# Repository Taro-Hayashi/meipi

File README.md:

# meipi

BOOTHで商品を購入すると付いてくることがあります。名刺代わりにお配りしているもので、組み立てるにもパーツを揃える必要がありますのでご随意にしていただければ幸いです。

## パーツリスト

### 共通パーツ
|Ref|部品名|
|-|-|
||キースイッチ|
||キーキャップ|
||CherryMXホットスワップソケット|
||1N4148W|
||MJ-4PP-9, PJ-320A|
|BOOT, RUN|3x6x4.3タクタイルスイッチ|
||Pro Micro|

### ロータリーエンコーダー
|Ref|部品名|
|-|-|
||EC11, EC12|
||ノブ|

### LED
|Ref|部品名|
|-|-|
|U1|NCP1117, ADP3338|
|LED0-12|SK6812MINI-E|

### OLED
|Ref|部品名|
|-|-|
||OLEDモジュール|
||ピンソケット 4ピン分|
||ピンヘッダ 4ピン分|

### トラックボール
|Ref|部品名|
|-|-|
||PIM447|
||3.5mmピンソケット 5ピン分|
||7mmスペーサー|
||ネジ|

### ジョイスティック
|Ref|部品名|
|-|-|
||RKJXV1224005 DIP化キット|
||キャップ|
|JOYSTICK0|L型ピンソケット 1x6（6p)|
|JOYSTICK1|ピンソケット 6ピン分|

### RP2040

頒布している基板には2種類あり、写真の位置に穴が空いている場合はRP2040の手はんだが可能です。
とても難しいので他のパーツより先にはんだ付けをしてください。
#### 表面実装部品
|Ref|部品名|
|-|-|
|RP2040|RP2040|
|U1|NCP1117, ADP3338|
|U2|W25Q（32MB〜）|
|USB0|USB Type-Cコネクタ 基板用|

#### 3225サイズ
|Ref|部品名|
|-|-|
|Y1|12MHz 水晶振動子|

#### 1206サイズ
|Ref|部品名|
|-|-|
|R1,2|5.1k|
|R3,4|27|
|R5|10k|
|R6-8|1k|
|C1,2|10u|
|C3|1u|
|C4,5|0.1u|
|C6|1u|
|C7-14|0.1u|
|C15,16|27p|

## ファームウェア
https://github.com/Taro-Hayashi/qmk_firmware/tree/tarohayashi/keyboards/tarohayashi/archive/meipi

### そのほか

atushi Morimoto様のフットプリントを改変、流用させていただきました。  
https://github.com/74th/rp2040-dev-board

takashicompany様のフットプリントを改変、流用させていただきました。  
https://github.com/takashicompany/tkbd-lib  
  
<br /><a rel="license" href="http://creativecommons.org/licenses/by-sa/4.0/">クリエイティブ・コモンズ 表示 - 継承 4.0 国際 ライセンス</a>の下に提供されています。

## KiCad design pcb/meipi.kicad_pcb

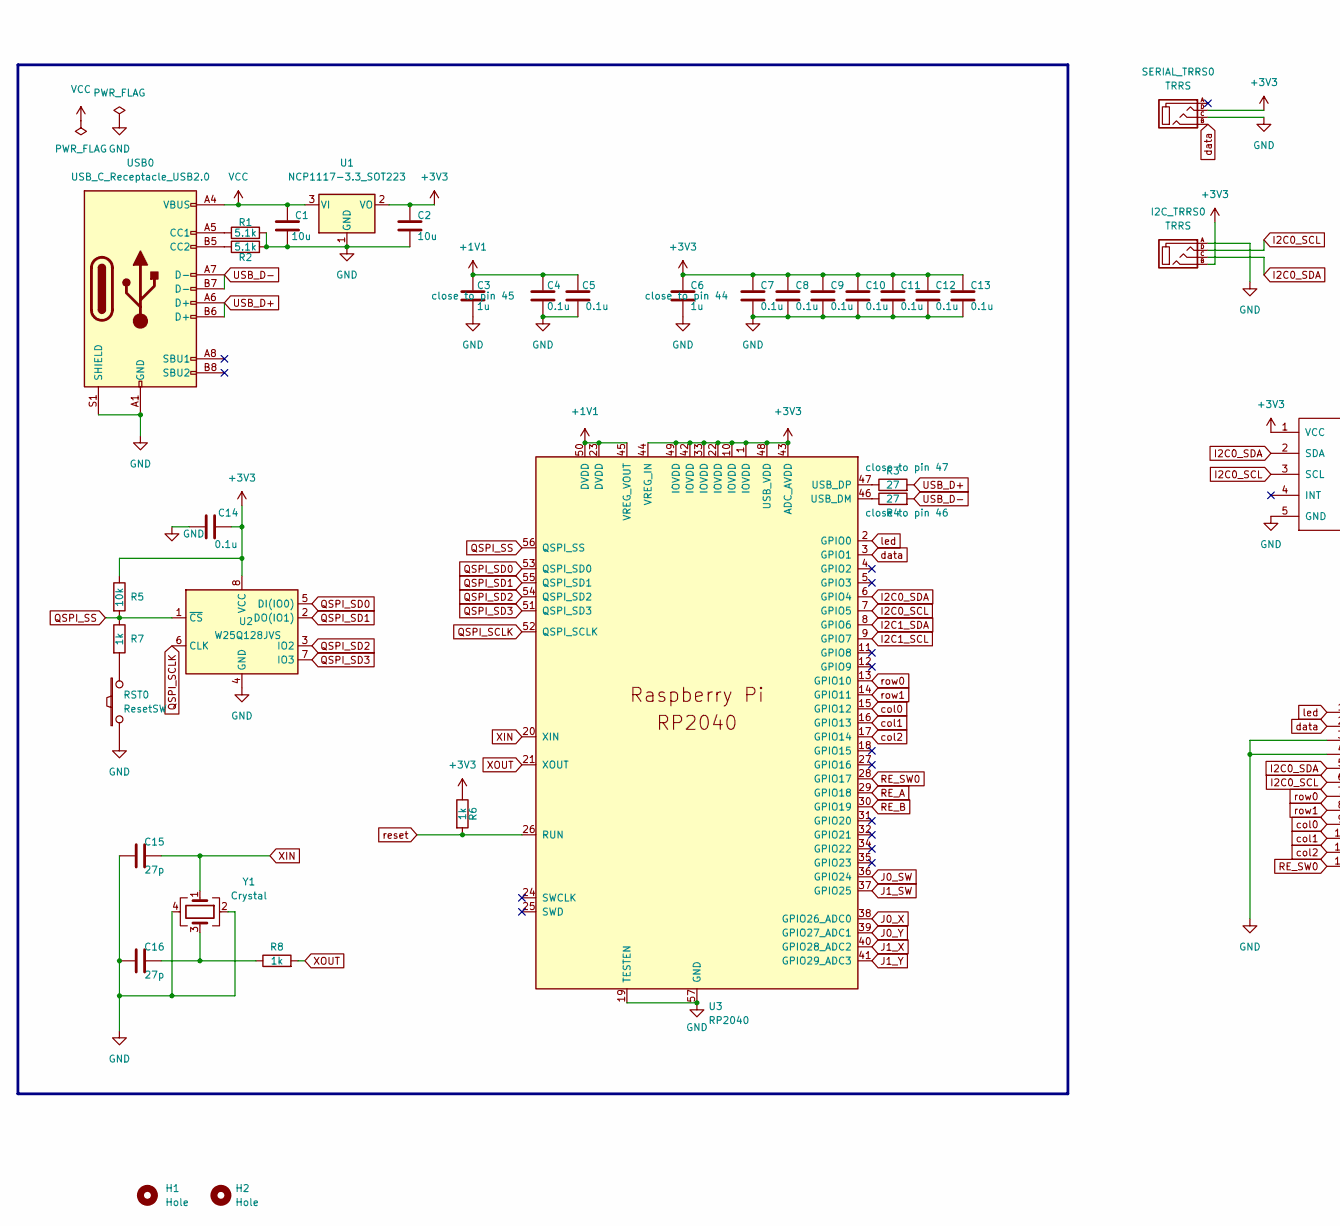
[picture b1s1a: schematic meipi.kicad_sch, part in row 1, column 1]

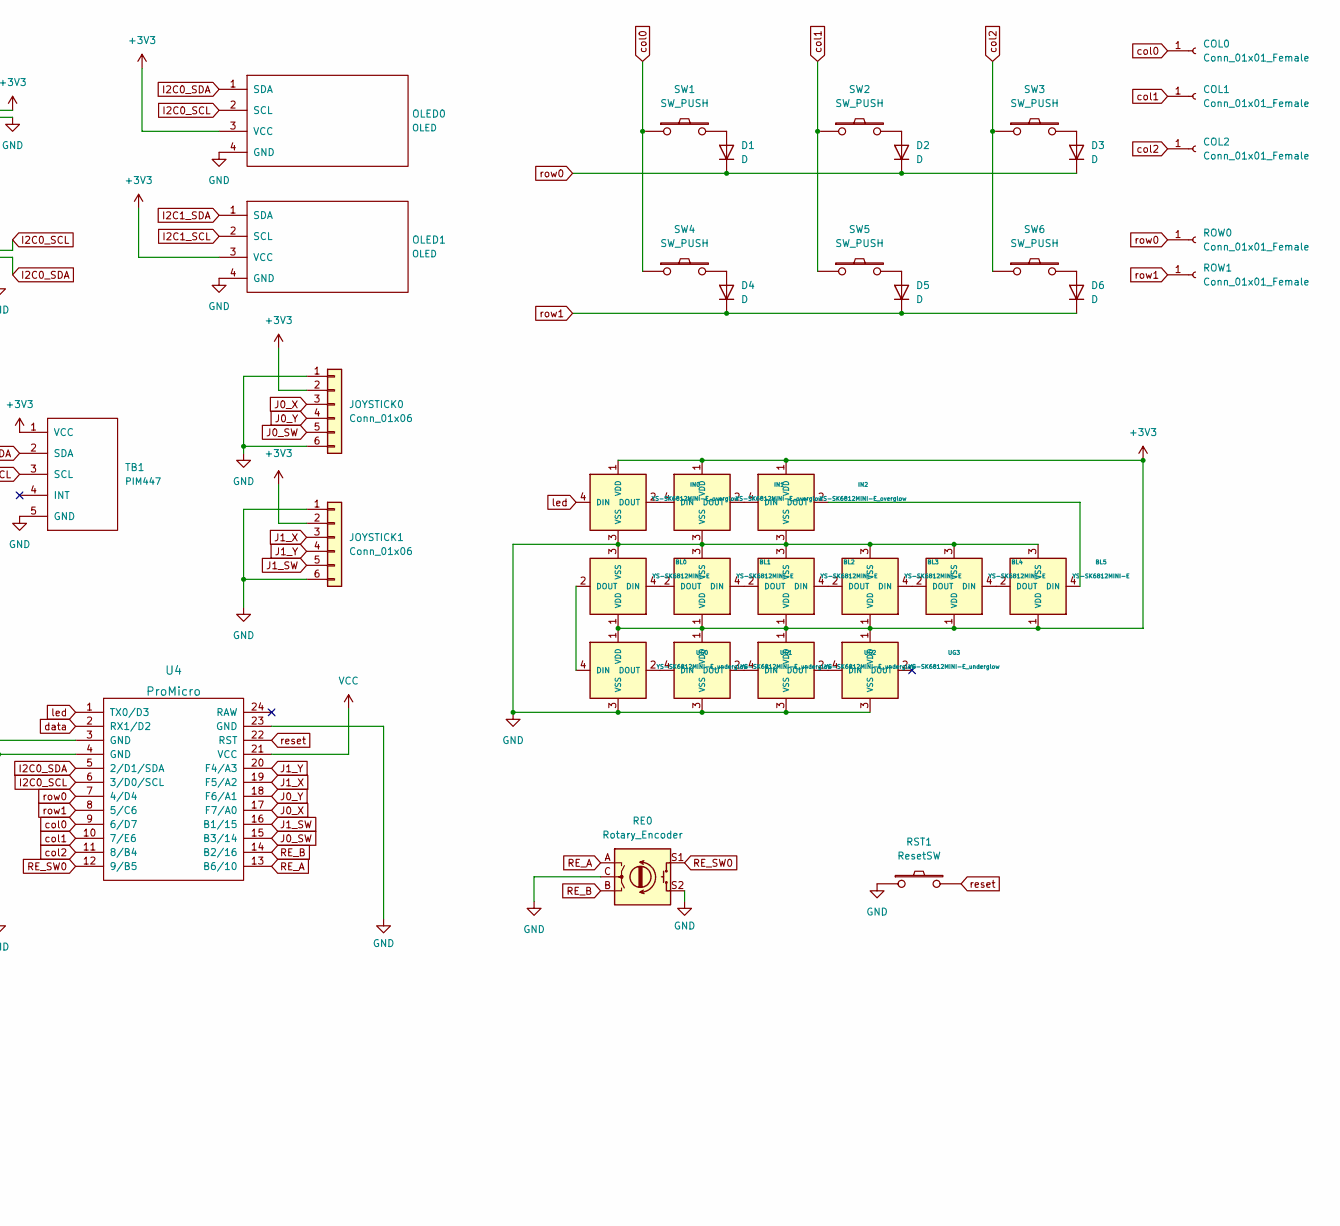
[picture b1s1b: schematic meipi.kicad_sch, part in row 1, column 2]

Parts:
BL0, BL1, BL2, BL3, BL4, BL5: YS-SK6812MINI-E
C1, C2: 10u; C_1206_3216_SMD
C3, C6: 1u; C_1206_3216_SMD
C4, C5, C7, C8, C9, C10, C11, C12, C13, C14: 0.1u; C_1206_3216_SMD
C15, C16: 27p; C_1206_3216_SMD
COL0, COL1, COL2: Conn_01x01_Female; Conn_1.3mm_M2
D1, D2, D3, D4, D5, D6: D; Diode_SMD
H1, H2: Hole; Hole_2.2mm_M2
I2C_TRRS0: TRRS
IN0, IN1, IN2: YS-SK6812MINI-E_overglow; YS-SK6812MINI-E
JOYSTICK0: Conn_01x06; PinSocket_1x06_P2.54mm_Horizontal
JOYSTICK1: Conn_01x06; PinHeader_1x06_P2.54mm_Vertical
OLED0, OLED1: OLED
R1, R2: 5.1k; R_1206_3216_SMD
R3, R4: 27; R_1206_3216_SMD
R5: 10k; R_1206_3216_SMD
R6, R7, R8: 1k; R_1206_3216_SMD
RE0: Rotary_Encoder; RotaryEncoder
ROW0, ROW1: Conn_01x01_Female; Conn_1.3mm_M2
RST0, RST1: ResetSW
SERIAL_TRRS0: TRRS
SW1, SW2, SW3, SW4, SW5, SW6: SW_PUSH; MXOnly-1U-Hotswap
TB1: PIM447
U1: NCP1117-3.3_SOT223; SOT-223-3_TabPin2
U2: W25Q128JVS; SOIC-8_5.23x5.23mm_P1.27mm
U3: RP2040; RP2040-QFN-56
U4: ProMicro; ProMicro_back_usd
UG0, UG1, UG2, UG3: YS-SK6812MINI-E_underglow; YS-SK6812MINI-E_Undergrow
USB0: USB_C_Receptacle_USB2.0
Y1: Crystal; Crystal_3225_SMD

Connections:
+1V1: C3.1, C4.1, C5.1, U3.23 (DVDD), U3.45 (VREG_VOUT), U3.50 (DVDD); also elsewhere on the board
+3V3: BL0.1 (VDD), BL1.1 (VDD), BL2.1 (VDD), BL3.1 (VDD), BL4.1 (VDD), BL5.1 (VDD), C2.1, C6.1, C7.1, C8.1, C9.1, C10.1, C11.1, C12.1, C13.1, C14.1, I2C_TRRS0.B, IN0.1 (VDD), IN1.1 (VDD), IN2.1 (VDD), JOYSTICK0.2, JOYSTICK1.2, OLED0.3 (VCC), OLED1.3 (VCC), R5.1, R6.1, SERIAL_TRRS0.D, TB1.1 (VCC), U1.2 (VO), U2.8 (VCC), U3.1 (IOVDD), U3.10 (IOVDD), U3.22 (IOVDD), U3.33 (IOVDD), U3.42 (IOVDD), U3.43 (ADC_AVDD), U3.44 (VREG_IN), U3.48 (USB_VDD), U3.49 (IOVDD), UG0.1 (VDD), UG1.1 (VDD), UG2.1 (VDD), UG3.1 (VDD); also elsewhere on the board
GND: BL0.3 (VSS), BL1.3 (VSS), BL2.3 (VSS), BL3.3 (VSS), BL4.3 (VSS), BL5.3 (VSS), C1.1, C2.2, C3.2, C4.2, C5.2, C6.2, C7.2, C8.2, C9.2, C10.2, C11.2, C12.2, C13.2, C14.2, C15.1, C16.1, I2C_TRRS0.A, IN0.3 (VSS), IN1.3 (VSS), IN2.3 (VSS), JOYSTICK0.1, JOYSTICK0.6, JOYSTICK1.1, JOYSTICK1.6, OLED0.4 (GND), OLED1.4 (GND), R1.2, R2.2, RE0.C, RE0.S2, RST0.1, RST1.1, SERIAL_TRRS0.C, TB1.5 (GND), U1.1 (GND), U2.4 (GND), U3.19 (TESTEN), U3.57 (GND), U4.3 (GND), U4.4 (GND), U4.23 (GND), UG0.3 (VSS), UG1.3 (VSS), UG2.3 (VSS), UG3.3 (VSS), USB0.A1 (GND), USB0.A12 (GND), USB0.B1 (GND), USB0.B12 (GND), USB0.S1 (SHIELD), Y1.2, Y1.4; also elsewhere on the board
I2C0_SCL: I2C_TRRS0.D, OLED0.2 (SCL), TB1.3 (SCL), U3.7 (GPIO5), U4.6 (3/D0/SCL); also elsewhere on the board
I2C0_SDA: I2C_TRRS0.C, OLED0.1 (SDA), TB1.2 (SDA), U3.6 (GPIO4), U4.5 (2/D1/SDA); also elsewhere on the board
I2C1_SCL: OLED1.2 (SCL), U3.9 (GPIO7); also elsewhere on the board
I2C1_SDA: OLED1.1 (SDA), U3.8 (GPIO6); also elsewhere on the board
J0_SW: JOYSTICK0.5, U3.36 (GPIO24), U4.15 (B3/14); also elsewhere on the board
J0_X: JOYSTICK0.3, U3.38 (GPIO26_ADC0), U4.17 (F7/A0); also elsewhere on the board
J0_Y: JOYSTICK0.4, U3.39 (GPIO27_ADC1), U4.18 (F6/A1); also elsewhere on the board
J1_SW: JOYSTICK1.5, U3.37 (GPIO25), U4.16 (B1/15); also elsewhere on the board
J1_X: JOYSTICK1.3, U3.40 (GPIO28_ADC2), U4.19 (F5/A2); also elsewhere on the board
J1_Y: JOYSTICK1.4, U3.41 (GPIO29_ADC3), U4.20 (F4/A3); also elsewhere on the board
unnamed: BL0.2 (DOUT), UG0.4 (DIN)
unnamed: BL0.4 (DIN), BL1.2 (DOUT)
unnamed: BL1.4 (DIN), BL2.2 (DOUT)
unnamed: BL2.4 (DIN), BL3.2 (DOUT)
unnamed: BL3.4 (DIN), BL4.2 (DOUT)
unnamed: BL4.4 (DIN), BL5.2 (DOUT)
unnamed: BL5.4 (DIN), IN2.2 (DOUT)
unnamed: C16.2, R8.1, Y1.3
unnamed: D1.2 (A), SW1.2
unnamed: D2.2 (A), SW2.2
unnamed: D3.2 (A), SW3.2
unnamed: D4.2 (A), SW4.2
unnamed: D5.2 (A), SW5.2
unnamed: D6.2 (A), SW6.2
unnamed: IN0.2 (DOUT), IN1.4 (DIN)
unnamed: IN1.2 (DOUT), IN2.4 (DIN)
unnamed 29: R3.1, U3.47 (USB_DP); also elsewhere on the board
unnamed 30: R4.1, U3.46 (USB_DM); also elsewhere on the board
unnamed: R7.2, RST0.2
unnamed: UG0.2 (DOUT), UG1.4 (DIN)
unnamed: UG1.2 (DOUT), UG2.4 (DIN)
unnamed: UG2.2 (DOUT), UG3.4 (DIN)
unnamed: R1.1, USB0.A5 (CC1)
unnamed: R2.1, USB0.B5 (CC2)
QSPI_SCLK: U2.6 (CLK), U3.52 (QSPI_SCLK); also elsewhere on the board
QSPI_SD0: U2.5 (DI(IO0)), U3.53 (QSPI_SD0); also elsewhere on the board
QSPI_SD1: U2.2 (DO(IO1)), U3.55 (QSPI_SD1); also elsewhere on the board
QSPI_SD2: U2.3 (IO2), U3.54 (QSPI_SD2); also elsewhere on the board
QSPI_SD3: U2.7 (IO3), U3.51 (QSPI_SD3); also elsewhere on the board
QSPI_SS: R5.2, R7.1, U2.1 (~CS), U3.56 (QSPI_SS); also elsewhere on the board
RE_A: RE0.A, U3.29 (GPIO18), U4.13 (B6/10); also elsewhere on the board
RE_B: RE0.B, U3.30 (GPIO19), U4.14 (B2/16); also elsewhere on the board
RE_SW0: RE0.S1, U3.28 (GPIO17), U4.12 (9/B5); also elsewhere on the board
USB_D+: R3.2, USB0.A6 (D+), USB0.B6 (D+)
USB_D-: R4.2, USB0.A7 (D-), USB0.B7 (D-)
VCC: C1.2, U1.3 (VI), U4.21 (VCC), USB0.A4 (VBUS), USB0.A9 (VBUS), USB0.B4 (VBUS), USB0.B9 (VBUS)
XIN: C15.2, U3.20 (XIN), Y1.1; also elsewhere on the board
XOUT: R8.2, U3.21 (XOUT); also elsewhere on the board
col0: COL0.1, SW1.1, SW4.1, U3.15 (GPIO12), U4.9 (6/D7); also elsewhere on the board
col1: COL1.1, SW2.1, SW5.1, U3.16 (GPIO13), U4.10 (7/E6); also elsewhere on the board
col2: COL2.1, SW3.1, SW6.1, U3.17 (GPIO14), U4.11 (8/B4); also elsewhere on the board
data: SERIAL_TRRS0.B, U3.3 (GPIO1), U4.2 (RX1/D2); also elsewhere on the board
led: IN0.4 (DIN), U3.2 (GPIO0), U4.1 (TX0/D3); also elsewhere on the board
reset: R6.2, RST1.2, U3.26 (RUN), U4.22 (RST); also elsewhere on the board
row0: D1.1 (K), D2.1 (K), D3.1 (K), ROW0.1, U3.13 (GPIO10), U4.7 (4/D4); also elsewhere on the board
row1: D4.1 (K), D5.1 (K), D6.1 (K), ROW1.1, U3.14 (GPIO11), U4.8 (5/C6); also elsewhere on the board

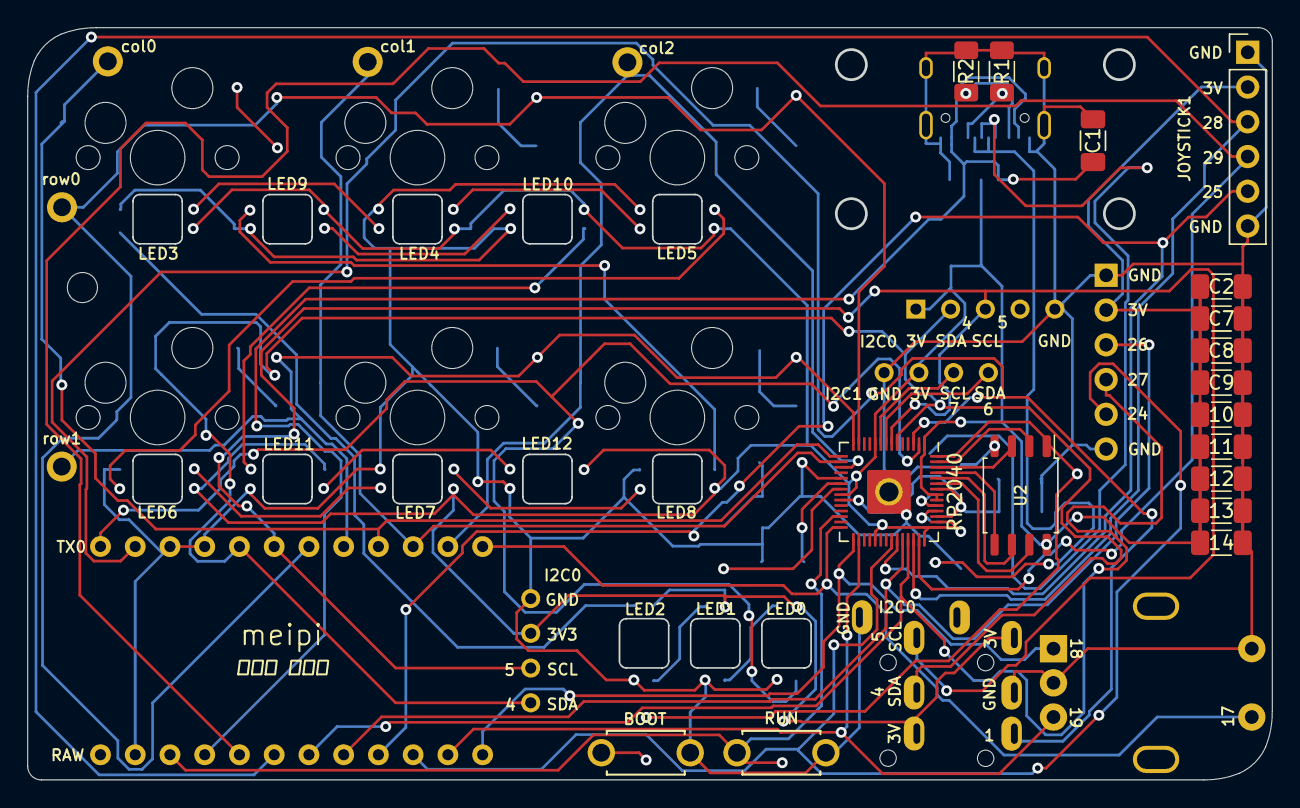
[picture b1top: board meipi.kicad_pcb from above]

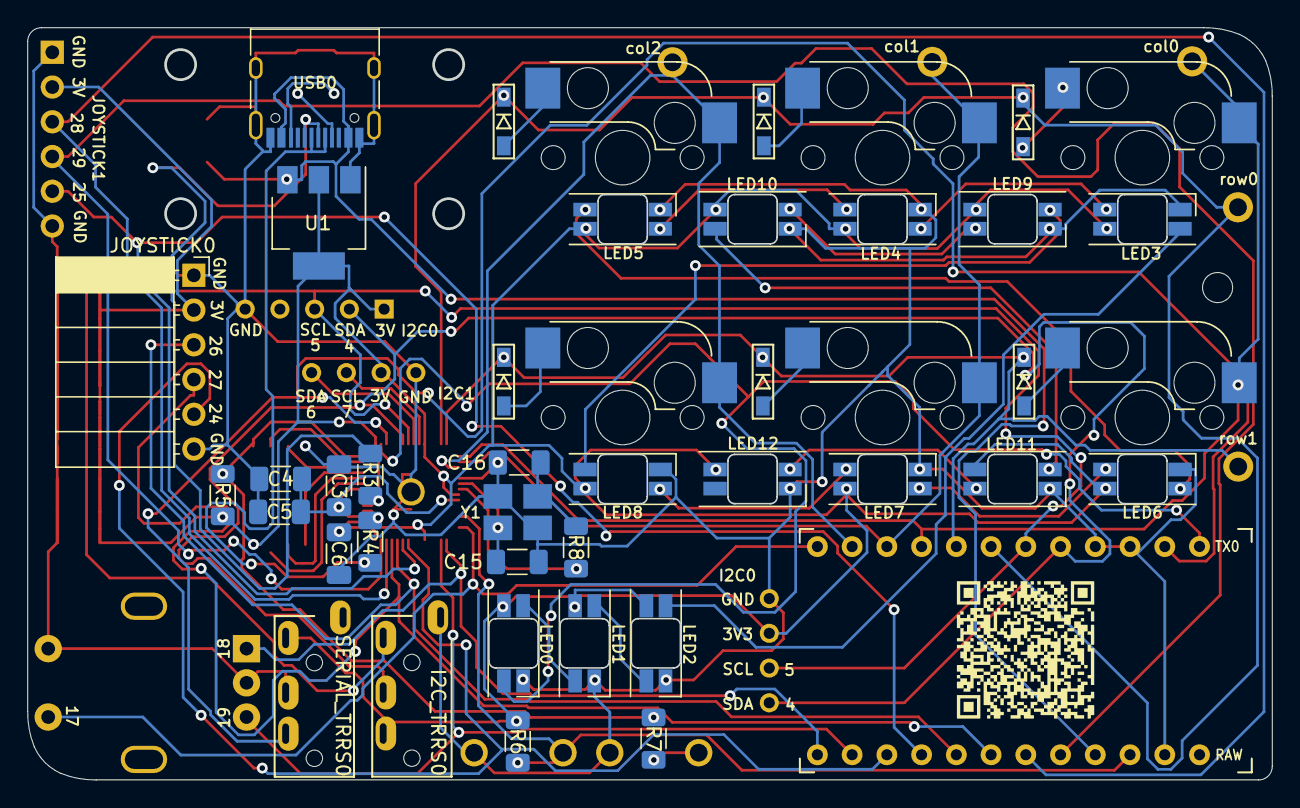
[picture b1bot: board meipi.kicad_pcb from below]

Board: 2 copper layers, 90.9 x 54.9 mm, 71 parts (33 on the bottom side), 59 nets.

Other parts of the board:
10, 11, 12, 13, 14: 0.1u; C_1206_3216_SMD
RP2040: RP2040; RP2040-QFN-56

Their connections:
+1V1: RP2040.23 (DVDD), RP2040.45 (VREG_VOUT), RP2040.50 (DVDD); also elsewhere on the board
+3V3: 10.1, 11.1, 12.1, 13.1, 14.1, RP2040.1 (IOVDD), RP2040.10 (IOVDD), RP2040.22 (IOVDD), RP2040.33 (IOVDD), RP2040.42 (IOVDD), RP2040.43 (ADC_AVDD), RP2040.44 (VREG_IN), RP2040.48 (USB_VDD), RP2040.49 (IOVDD); also elsewhere on the board
GND: 10.2, 11.2, 12.2, 13.2, 14.2, RP2040.19 (TESTEN), RP2040.57 (GND); also elsewhere on the board
I2C0_SCL: RP2040.7 (GPIO5); also elsewhere on the board
I2C0_SDA: RP2040.6 (GPIO4); also elsewhere on the board
I2C1_SCL: RP2040.9 (GPIO7); also elsewhere on the board
I2C1_SDA: RP2040.8 (GPIO6); also elsewhere on the board
J0_SW: RP2040.36 (GPIO24); also elsewhere on the board
J0_X: RP2040.38 (GPIO26_ADC0); also elsewhere on the board
J0_Y: RP2040.39 (GPIO27_ADC1); also elsewhere on the board
J1_SW: RP2040.37 (GPIO25); also elsewhere on the board
J1_X: RP2040.40 (GPIO28_ADC2); also elsewhere on the board
J1_Y: RP2040.41 (GPIO29_ADC3); also elsewhere on the board
unnamed 29: RP2040.47 (USB_DP); also elsewhere on the board
unnamed 30: RP2040.46 (USB_DM); also elsewhere on the board
QSPI_SCLK: RP2040.52 (QSPI_SCLK); also elsewhere on the board
QSPI_SD0: RP2040.53 (QSPI_SD0); also elsewhere on the board
QSPI_SD1: RP2040.55 (QSPI_SD1); also elsewhere on the board
QSPI_SD2: RP2040.54 (QSPI_SD2); also elsewhere on the board
QSPI_SD3: RP2040.51 (QSPI_SD3); also elsewhere on the board
QSPI_SS: RP2040.56 (QSPI_SS); also elsewhere on the board
RE_A: RP2040.29 (GPIO18); also elsewhere on the board
RE_B: RP2040.30 (GPIO19); also elsewhere on the board
RE_SW0: RP2040.28 (GPIO17); also elsewhere on the board
XIN: RP2040.20 (XIN); also elsewhere on the board
XOUT: RP2040.21 (XOUT); also elsewhere on the board
col0: RP2040.15 (GPIO12); also elsewhere on the board
col1: RP2040.16 (GPIO13); also elsewhere on the board
col2: RP2040.17 (GPIO14); also elsewhere on the board
data: RP2040.3 (GPIO1); also elsewhere on the board
led: RP2040.2 (GPIO0); also elsewhere on the board
reset: RP2040.26 (RUN); also elsewhere on the board
row0: RP2040.13 (GPIO10); also elsewhere on the board
row1: RP2040.14 (GPIO11); also elsewhere on the board

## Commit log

2023-02-23 code

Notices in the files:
README.md:
CC BY-SA 4.0
